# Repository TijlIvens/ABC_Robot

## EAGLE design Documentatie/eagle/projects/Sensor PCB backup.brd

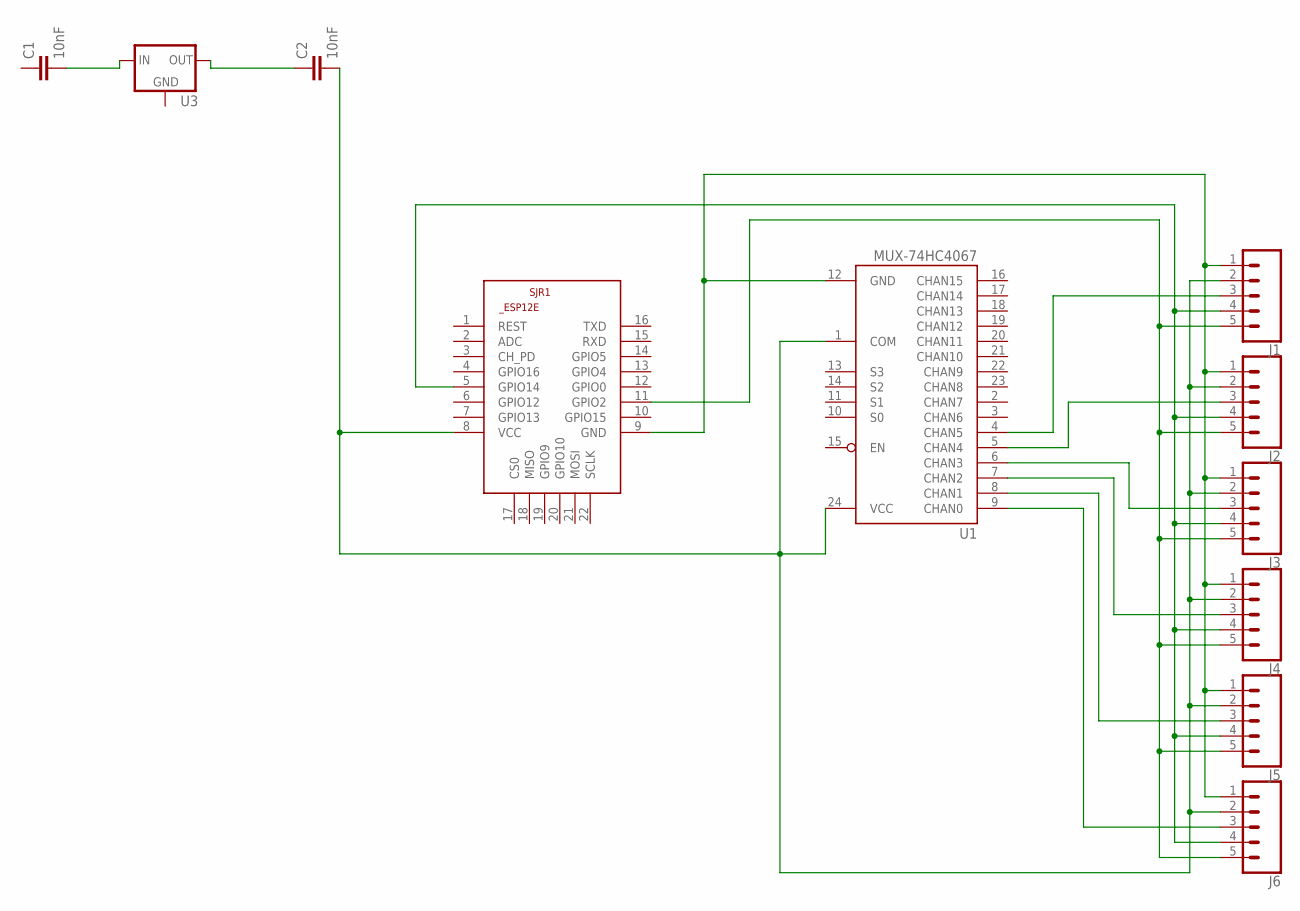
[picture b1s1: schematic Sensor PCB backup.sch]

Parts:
C1, C2: 10nF; 0603
J1, J2, J3, J4, J5, J6: CONN_05SMD; 1X05_1MM
SJR1: ESP8266-12EESP12E; ESP8266-ESP12E
U1: MUX-74HC4067; SSOP24
U3: V_REG_78XX-TO-220; TO-220-ALT

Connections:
unnamed: C1.2, U3.IN
unnamed: C2.1, U3.OUT
unnamed: C2.2, J1.2, J2.2, J3.2, J4.2, J5.2, J6.2, SJR1.8 (VCC), U1.1 (COM), U1.24 (VCC)
unnamed: J3.3, U1.6 (CHAN3)
unnamed: J1.3, U1.4 (CHAN5)
unnamed: J2.3, U1.5 (CHAN4)
unnamed: J4.3, U1.7 (CHAN2)
unnamed: J5.3, U1.8 (CHAN1)
unnamed: J6.3, U1.9 (CHAN0)
unnamed: J1.5, J2.5, J3.5, J4.5, J5.5, J6.5, SJR1.11 (GPIO2)
unnamed: J1.4, J2.4, J3.4, J4.4, J5.4, J6.4, SJR1.5 (GPIO14)
unnamed: J1.1, J2.1, J3.1, J4.1, J5.1, J6.1, SJR1.9 (GND), U1.12 (GND)

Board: 2 copper layers, 11 parts (0 on the bottom side), 12 nets, no tracks yet.

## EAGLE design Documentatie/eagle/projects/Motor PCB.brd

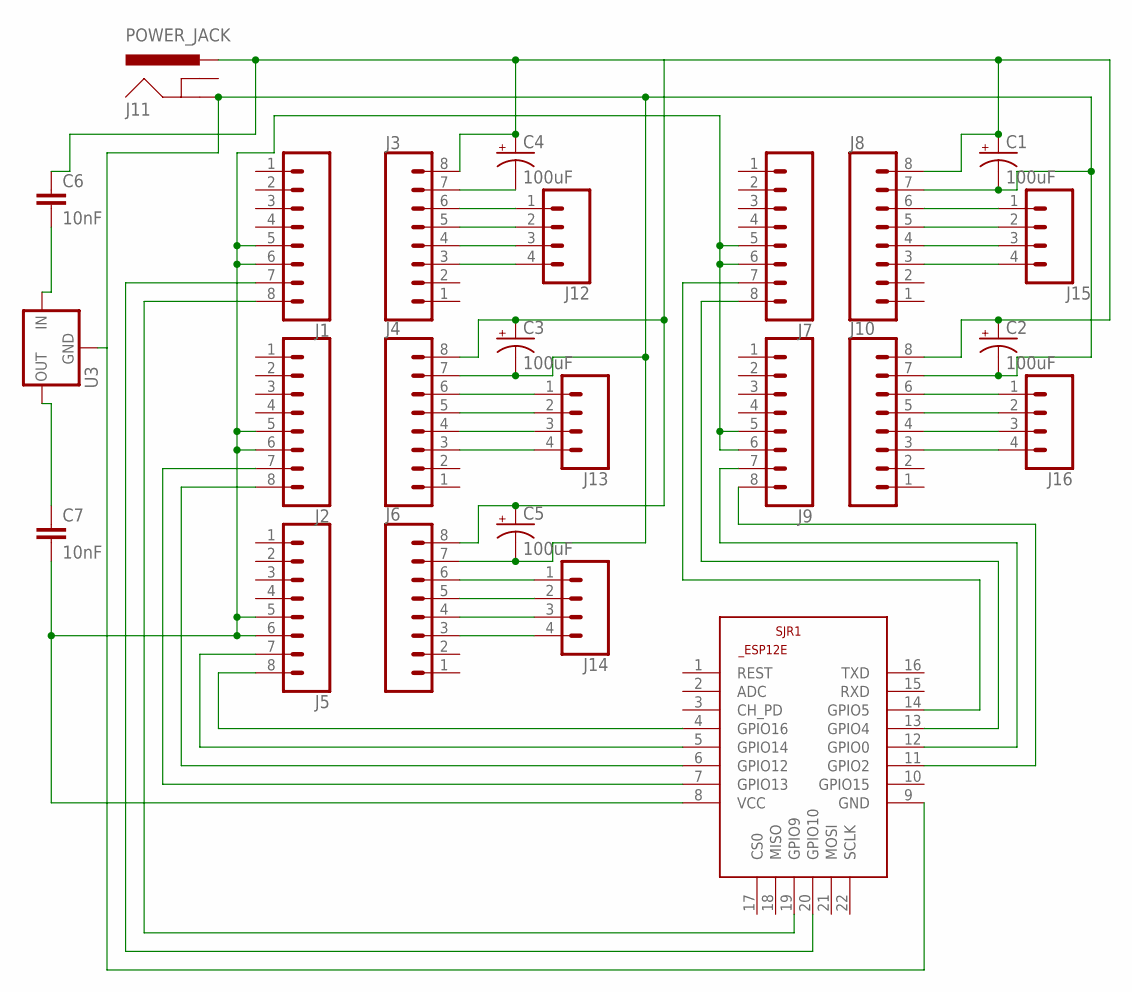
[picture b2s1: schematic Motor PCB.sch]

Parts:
C1, C2, C3, C4, C5: 100uF; EIA7343
C6, C7: 10nF; 0603
J1, J2, J3, J4, J5, J6, J7, J8, J9, J10: CONN_08"; 1X08
J11: POWER_JACK; POWER_JACK_PTH
J12, J13, J14, J15, J16: CONN_04JST-PTH-VERT; JST-4-PTH-VERT
SJR1: ESP8266-12EESP12E; ESP8266-ESP12E
U3: V_REG_78XX-TO-220; TO-220-ALT

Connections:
unnamed: C1.A (+), C2.A (+), C3.A (+), C4.A (+), C5.A (+), C6.1, J3.8, J4.8, J6.8, J8.8, J10.8, J11.PWR
unnamed: J4.6, J13.1
unnamed: J9.8, SJR1.11 (GPIO2)
unnamed: J9.7, SJR1.12 (GPIO0)
unnamed: J7.8, SJR1.13 (GPIO4)
unnamed: C4.C (-), J3.7
unnamed: J7.7, SJR1.14 (GPIO5)
unnamed: J1.7, SJR1.20 (GPIO10)
unnamed: J1.8, SJR1.19 (GPIO9)
unnamed: J2.7, SJR1.7 (GPIO13)
unnamed: J2.8, SJR1.6 (GPIO12)
unnamed: J5.7, SJR1.5 (GPIO14)
unnamed: J5.8, SJR1.4 (GPIO16)
unnamed: J3.6, J12.1
unnamed: J3.5, J12.2
unnamed: J3.4, J12.3
unnamed: J3.3, J12.4
unnamed: C1.C (-), C2.C (-), C3.C (-), C5.C (-), J4.7, J6.7, J8.7, J10.7, J11.GND, SJR1.9 (GND), U3.GND
unnamed: J4.5, J13.2
unnamed: J4.4, J13.3
unnamed: J4.3, J13.4
unnamed: J6.6, J14.1
unnamed: J6.5, J14.2
unnamed: J6.4, J14.3
unnamed: J6.3, J14.4
unnamed: J8.6, J15.1
unnamed: J8.5, J15.2
unnamed: J8.4, J15.3
unnamed: J8.3, J15.4
unnamed: J10.6, J16.1
unnamed: J10.5, J16.2
unnamed: J10.4, J16.3
unnamed: J10.3, J16.4
unnamed: C6.2, U3.IN
unnamed: C7.1, U3.OUT
unnamed: C7.2, J1.5, J1.6, J2.5, J2.6, J5.5, J5.6, J7.5, J7.6, J9.5, J9.6, SJR1.8 (VCC)

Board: 2 copper layers, 25 parts (0 on the bottom side), 36 nets, no tracks yet.

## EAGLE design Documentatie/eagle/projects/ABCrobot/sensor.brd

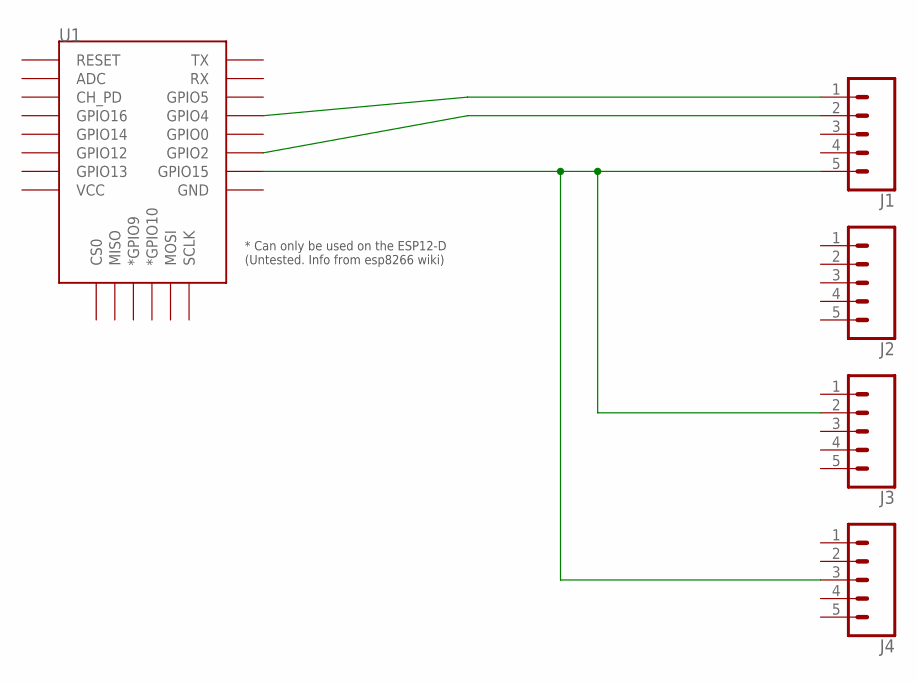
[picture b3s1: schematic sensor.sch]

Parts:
J1, J2, J3, J4: CONN_05SMD; 1X05_1MM
U1: ESP12ESMD; ESP12E-SMD

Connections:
unnamed: J1.1, U1.GPIO4
unnamed: J1.2, U1.GPIO2
unnamed: J1.5, J3.2, J4.3, U1.GPIO15

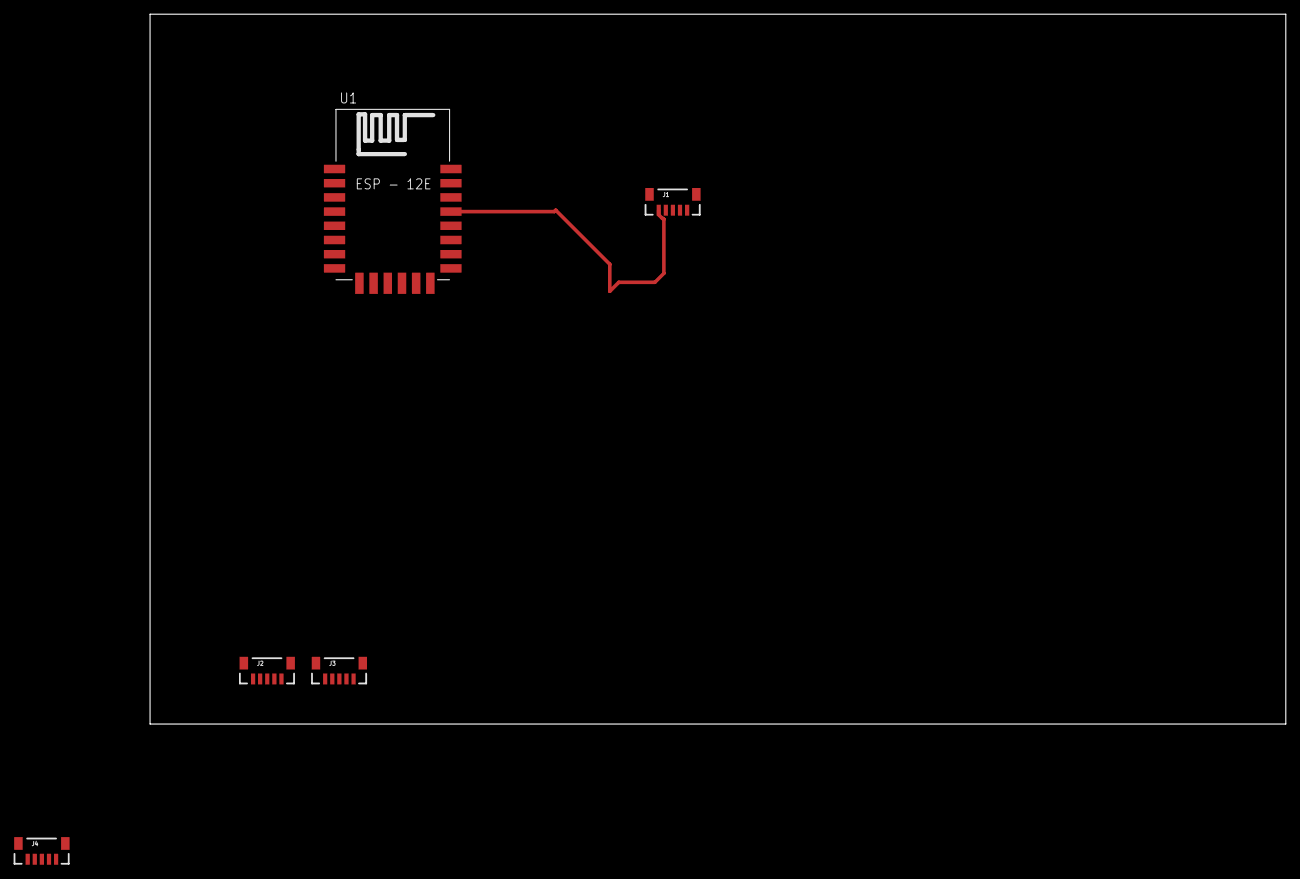
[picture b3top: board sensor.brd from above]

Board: 2 copper layers, 160.0 x 100.0 mm, 5 parts (0 on the bottom side), 3 nets.

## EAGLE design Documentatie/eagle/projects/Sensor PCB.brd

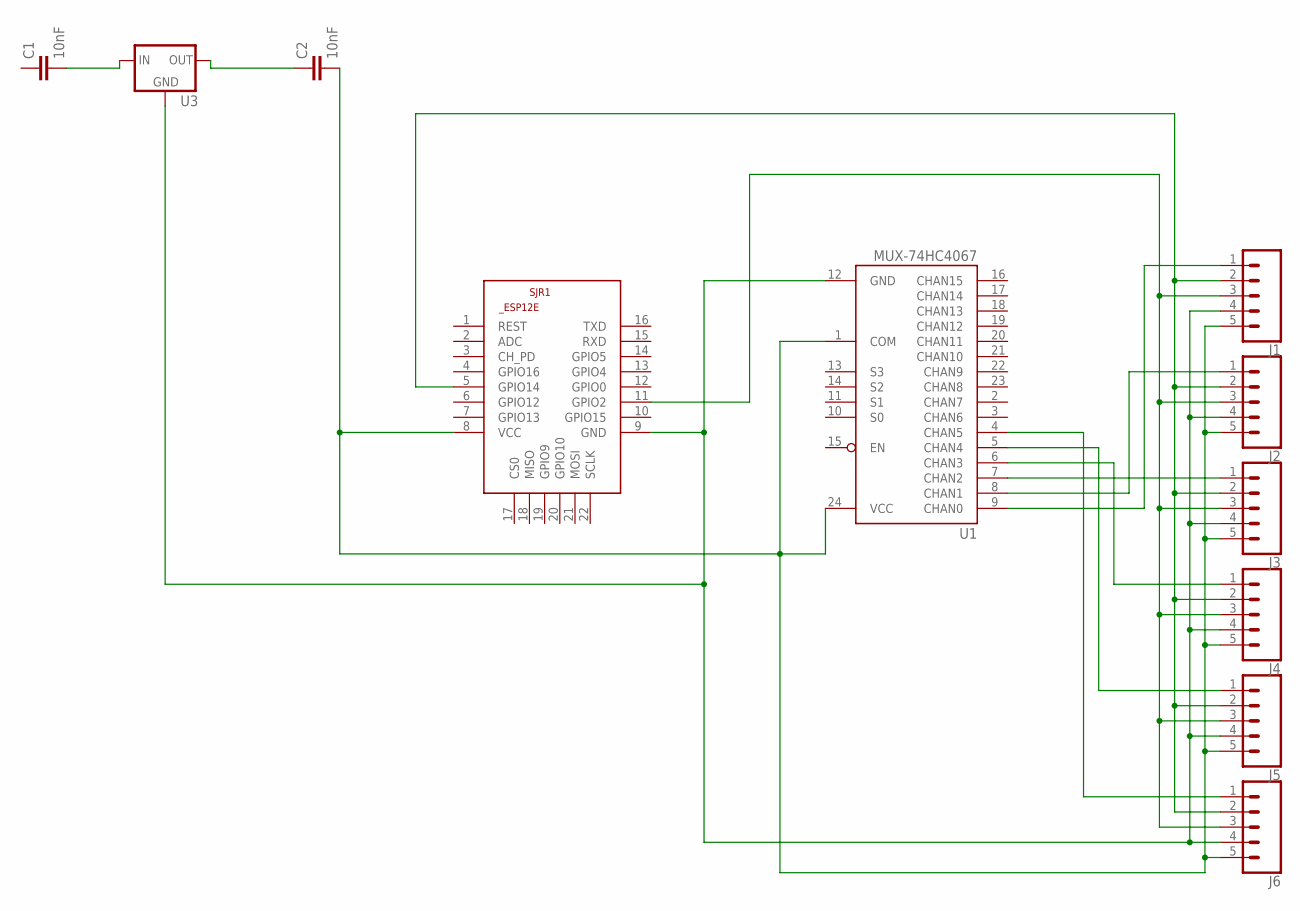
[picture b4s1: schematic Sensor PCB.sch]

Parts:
C1, C2: 10nF; 0603
J1, J2, J3, J4, J5, J6: CONN_05JST-VERT; JST-5-PTH-VERT
SJR1: ESP8266-12EESP12E; ESP8266-ESP12E
U1: MUX-74HC4067; SSOP24
U3: V_REG_78XX-TO-220; TO-220-ALT

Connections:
unnamed: C1.2, U3.IN
unnamed: C2.1, U3.OUT
unnamed: C2.2, J1.5, J2.5, J3.5, J4.5, J5.5, J6.5, SJR1.8 (VCC), U1.1 (COM), U1.24 (VCC)
unnamed: J6.1, U1.4 (CHAN5)
unnamed: J1.3, J2.3, J3.3, J4.3, J5.3, J6.3, SJR1.11 (GPIO2)
unnamed: J1.2, J2.2, J3.2, J4.2, J5.2, J6.2, SJR1.5 (GPIO14)
unnamed: J1.1, U1.9 (CHAN0)
unnamed: J1.4, J2.4, J3.4, J4.4, J5.4, J6.4, SJR1.9 (GND), U1.12 (GND), U3.GND
unnamed: J2.1, U1.8 (CHAN1)
unnamed: J3.1, U1.7 (CHAN2)
unnamed: J4.1, U1.6 (CHAN3)
unnamed: J5.1, U1.5 (CHAN4)

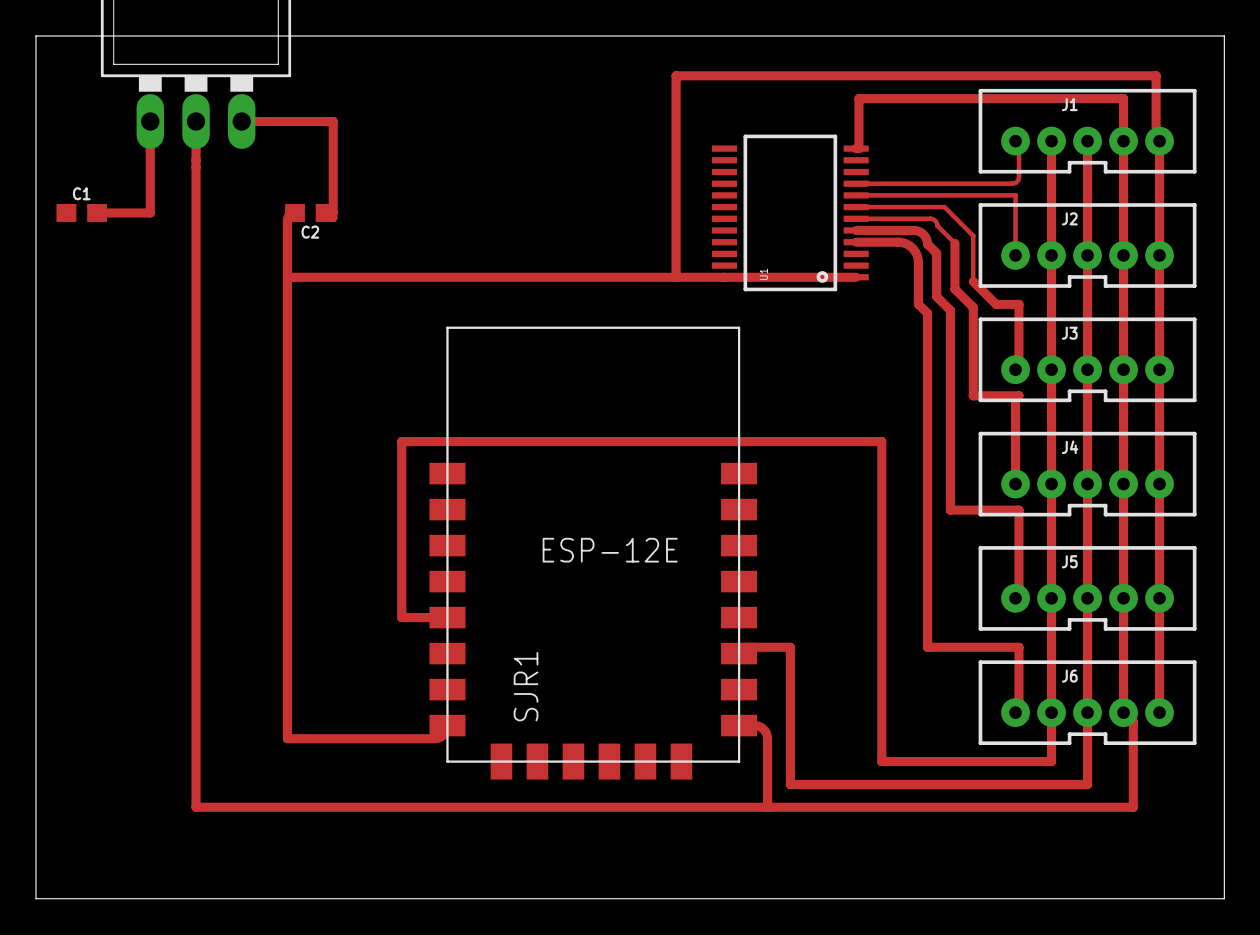
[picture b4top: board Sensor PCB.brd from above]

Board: 2 copper layers, 66.0 x 47.9 mm, 11 parts (0 on the bottom side), 12 nets.

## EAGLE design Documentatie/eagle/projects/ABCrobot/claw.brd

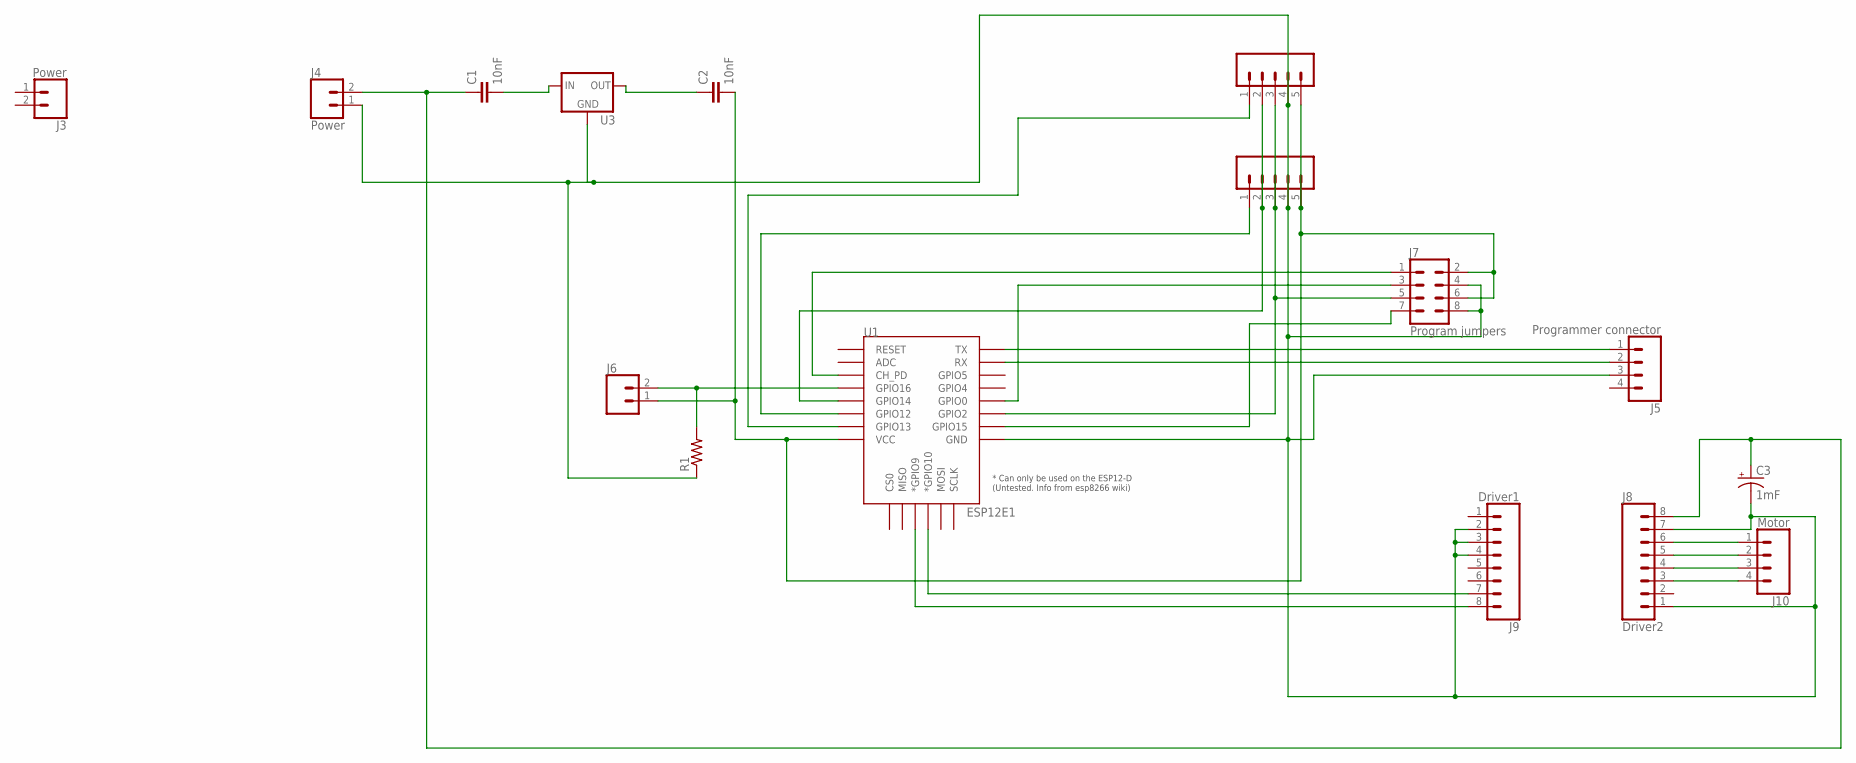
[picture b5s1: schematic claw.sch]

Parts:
C1, C2: 10nF; 0603
C3: 1mF; CPOL-RADIAL-5MM-10MM
J1: Sensor1; JST-5-PTH-VERT
J2: Sensor2; JST-5-PTH-VERT
J3, J4: Power; 1X02_LOCK
J5: Programmer connector; JST-4-PTH-VERT
J6: CONN_02LOCK; 1X02_LOCK
J7: Program jumpers; 2X4
J8: Driver2; 1X08_NO_SILK
J9: Driver1; 1X08_NO_SILK
J10: Motor; JST-4-PTH-VERT
R1: R-US_M2309; M2309
U1: ESP12E1; ESP12E-SMD
U3: V_REG_78XX-TO-220; TO-220-ALT

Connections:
unnamed: C3.-, J1.4, J2.4, J4.1, J5.3, J7.4, J7.8, J8.1, J8.7, J9.2, J9.3, J9.4, R1.1, U1.GND, U3.GND
unnamed: J1.3, J2.3, J7.5, U1.GPIO2
unnamed: J1.2, J2.2, U1.GPIO14
unnamed: J1.1, U1.GPIO13
unnamed: J2.1, U1.GPIO12
unnamed: J8.6, J10.1
unnamed: C1.2, U3.IN
unnamed: C2.1, U3.OUT
unnamed: C2.2, J1.5, J2.5, J6.1, J7.2, J7.6, U1.VCC
unnamed: J8.5, J10.2
unnamed: J8.4, J10.3
unnamed: J8.3, J10.4
unnamed: J9.8, U1.GPIO9 (*GPIO9)
unnamed: J9.7, U1.GPIO10 (*GPIO10)
unnamed: C1.1, C3.+, J4.2, J8.8
unnamed: J5.1, U1.TXD0 (TX)
unnamed: J5.2, U1.RXD0 (RX)
unnamed: J7.7, U1.GPIO15
unnamed: J7.3, U1.GPIO0
unnamed: J7.1, U1.CH_PD
unnamed: J6.2, R1.2, U1.GPIO16

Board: 2 copper layers, 16 parts (0 on the bottom side), 21 nets, no tracks yet.

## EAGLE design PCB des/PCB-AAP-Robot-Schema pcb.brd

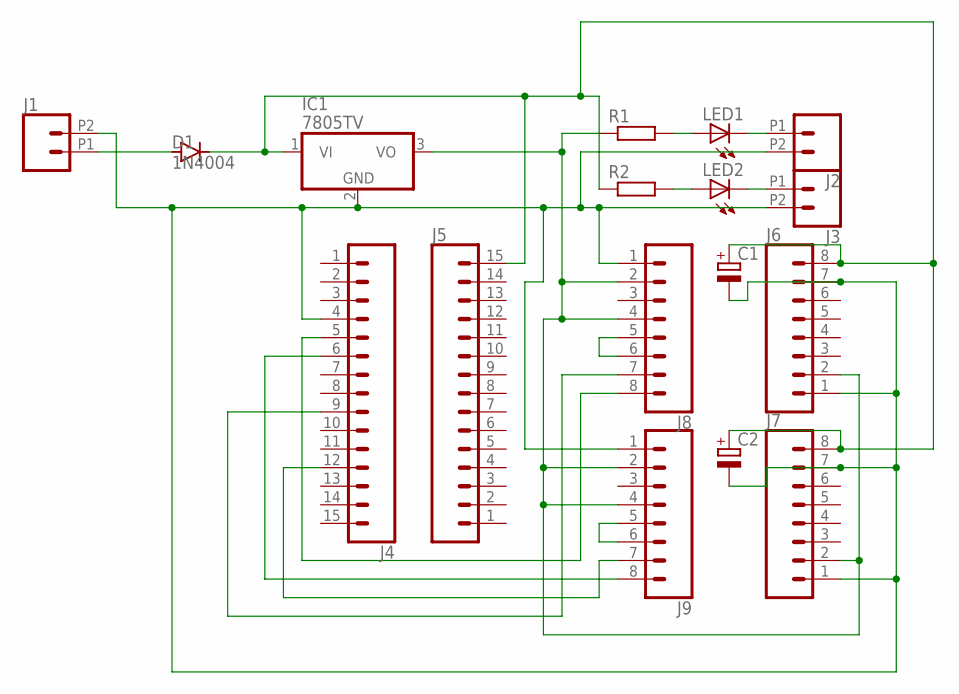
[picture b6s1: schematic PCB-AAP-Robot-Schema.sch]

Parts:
C1, C2: CPOL-EUB; PANASONIC_B
D1: 1N4004; DO41-10
IC1: 7805TV; TO220V
J1, J2, J3: CONN_022.54MM_SCREWTERM; 1X02_2.54_SCREWTERM
J4, J5: CONN_15; 1X15
J6, J7, J8, J9: CONN_08"; 1X08
LED1, LED2: LED3MM
R1, R2: R-EU_0207/10; 0207/10

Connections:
unnamed: C1.+, C2.+, D1.C, IC1.1 (VI), J5.15, J6.8, J7.8, R2.1
unnamed: D1.A, J1.P1 (1)
unnamed: J4.6, J9.8
unnamed: LED1.A, R1.2
unnamed: C1.-, C2.-, IC1.2 (GND), J1.P2 (2), J2.P2 (2), J3.P2 (2), J4.4, J6.1, J6.7, J7.1, J7.7, J8.1, J9.1
unnamed: J2.P1 (1), LED1.K (C)
unnamed: J4.5, J8.8
unnamed: J4.12, J9.7
unnamed: J4.9, J8.7
unnamed: J8.5, J8.6
unnamed: J9.5, J9.6
unnamed: LED2.A, R2.2
unnamed: IC1.3 (VO), J6.2, J7.2, J8.2, J8.4, J9.2, J9.4, R1.1
unnamed: J3.P1 (1), LED2.K (C)

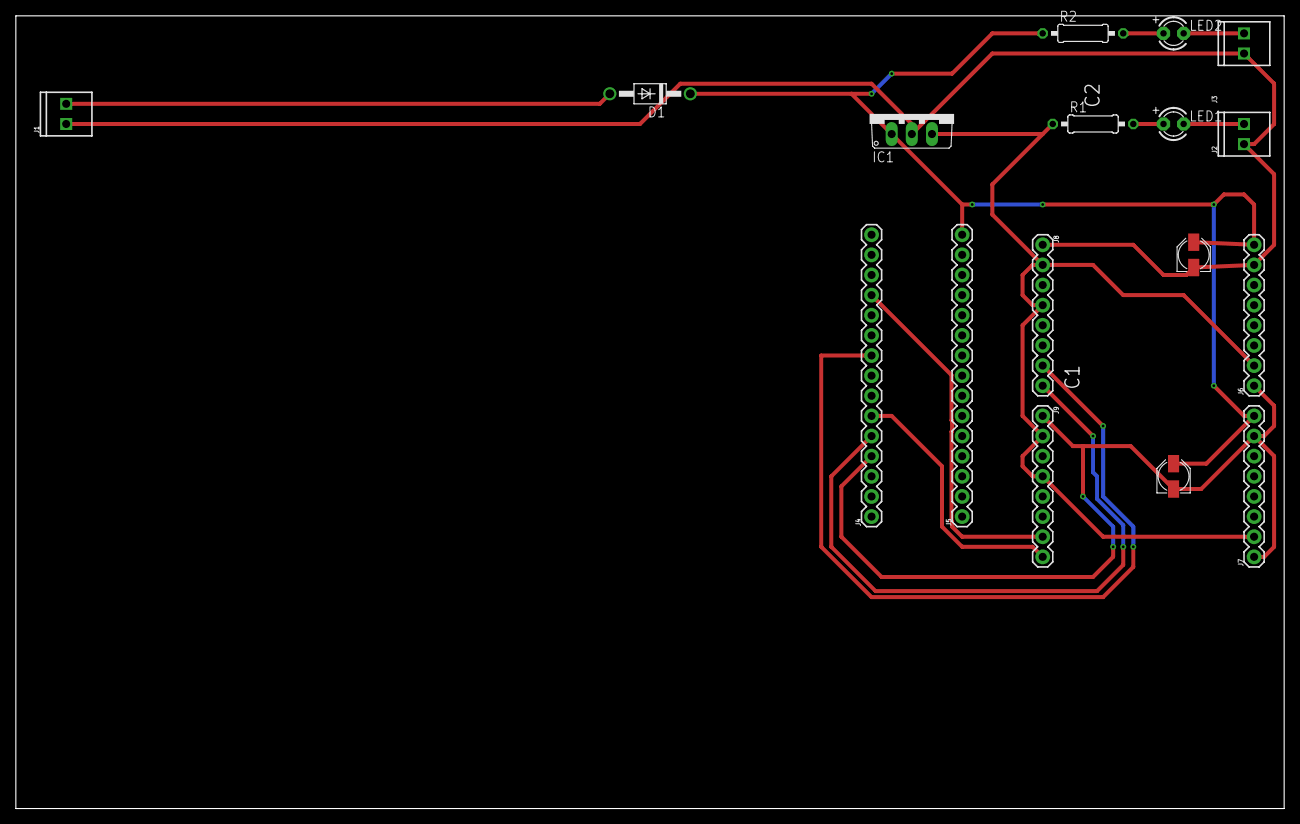
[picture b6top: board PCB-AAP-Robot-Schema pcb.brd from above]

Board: 2 copper layers, 160.0 x 100.0 mm, 17 parts (0 on the bottom side), 14 nets.

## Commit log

2019-02-25 Feather Sensor
2019-02-28 test program for the drive module
2019-03-01 Made a folder for belt
    Added arduino belt program and a test program for the feather to communicate with the arduino belt program
2019-03-14 Working communication between feather and arduino
    Communication between them with I2C works and also transferring the received data to usefull data works.
2019-03-18 basic belt program done
2019-05-28 soort van software teller issues ...
    ga de code drastisch aanpassen ==> updatje
2019-05-29 Other Timer/Counter logic
    first there was a software timer that increased every time there was a compare match interrupt. Now in the interrupts there wil be sent to which number the TCNT registers has to count and also if the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
2019-05-29 raspberry datalogger af
    added raspberry pi code en documentatie
2019-05-29 TestProgram drive foward and backward
2019-05-29 changed prescaler and microstepping
2019-05-29 Poging tot sensor
2019-06-03 Mappen juist
2019-06-05 files van Belt map gekopieerd naar Drive map
    Omdat uiteindelijk gebruik werd gemaakt van stappenmotoren ipv dc motoren en ik al een basic programma had in de Belt map voor stappen motoren heb ik aan deze verder gewerkt. Deze hoorde dus in de Dr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
2019-06-05 Documentation Added
2019-06-05 PCB design en 3D ontwerp

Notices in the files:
parts and their libraries:
SparkFun-Connectors: Licensing: Creative Commons ShareAlike 4.0 International - https://creativecommons.org/licenses/by-sa/4.0
